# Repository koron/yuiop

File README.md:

# YUIOP Keyboard series

YUIOP keyboards are experimental original keyboards designed by KoRoN.

## Sub Projects

Keyboards in this project are:

*   yuiop27/ - separate keyboard prototype.

    27 keys for one hand. single left hand.

*   yuiop54/main - signle board keyboard prototype.

    combined right and left-hand boards of yuiop27.
    PCB dimension is 285.00mm x 94.60mm (GH60 compatible form factor without
    screw holes).

*   yuiop54/main2 - researching version of yuiop54.

    multi-sheets schematic.
    fix layout for auto routing.
    introduce GND cupper fill.
    *   rev.B - trial to make compatible with GH60 (include screw holes).

        use popular keycaps size.
        tring 128x64 dots OLED.
    *   rev.C - key sizes revised version.

        consider just layout.
        use 1u footprint for keys of little fingers. 
        compact form factor size, 267.00mm x 95.00mm (drop compatibility with
        GH60).
        change the origin to center of PCB.
        use 2u for R5 center key.
        use Edge.Cuts to represents screw holes.
        OLED is 128x32 dots.
    *   rev.D - narrowwer version of rev.C

        consider just layout.
        the dimension is 262.0mm x 95.00mm
        reduce margins between `F` and `G` keys, and `H` and `J` keys.
    *   rev.E - a variation of rev.C

        the dimension is 267.00mm x 95.00mm (same with rev.C, not rev.D)
        make keys on `F`'s row be able to use 1.25u keycap.

*   yuiop47/ - Single board keyborard with 47 keys.

    Shrink from yuiop54.
    PCB dimension is 214.00mm x 94.00mm

*   yuiop60hh/main - HHKB clone trial

    * main2 - HHKB clone trial #2
    * main3
    * main4
    * main5 - Practicing version
    * main5b - USB Type-C receptacle version of main5

*   yuiop50d/ - Small footprint, dense 50 keys keyboard.

    1u is 16mm, using small keycaps.
    Standard row staggered layout.
    Support Pro Micro and RapsberryPi Pico as MCU.
    PCB dimension is 182.00mm x 103.50mm

*   yuiop63hhs/ - Split HHKB layout minimal keyboard.

    No LED nor OLED, Just 63 (29+34) keys.
    PCB dimension 319.00mm x 95.00mm
    *   Left 152.50mm x 95.00mm
    *   Right 162.00mm x 95.00mm

*   yuiop22rs/ - 22 keys + rotary switch macropad.

    With OLED, without LED.
    PCB dimension 95.25mm x 95.25mm

*   contorller/ - Keyboard controler using ATmega32U4 which replacing Pro
    Micro.

*   yuiopPM/ - Pro Micro compatible but minimal for only keyboard, PCB

*   yuiopPM2/ - Revised version of yuiopPM. It was shelved unfinished.

*   yuiop60hh/main3 - HHKB layout, compatible with popular 60% cases.

    Problems on positions of screw hole or so. Not built.

*   yuiop60hh/main4 - HHKB layout, compatible with popular 60% cases.

    YUIOP60HH series revision 4.
    Implemented with MPU ATmega32U4 (not Pro Micro)

*   yuiop31rs/ - 31 keys + rotary switch macropad.

    With 31 LEDs (WB2812C-2020). Its hole is too small to be chaged extra on
    production.

*   yuiop60s/ - split keyboard prototype

*   yuiop60pi/ - PGA2040 (RP2040) base HHKB layout semi-compatible keyboard.

*   yuiop2040/ - Original RP2040 control board.

*   yuiop2040C/ "Compact" model of yuiop2040. Abandoned.

*   yuiop32dm/ - Experimental keyboard for Duplic Matrix

*   yuiopPD/ - Pointing device using the trackball module of Keyball series.

*   rp2040-controller/ - Reusable circuit diagram for controller using RP2040

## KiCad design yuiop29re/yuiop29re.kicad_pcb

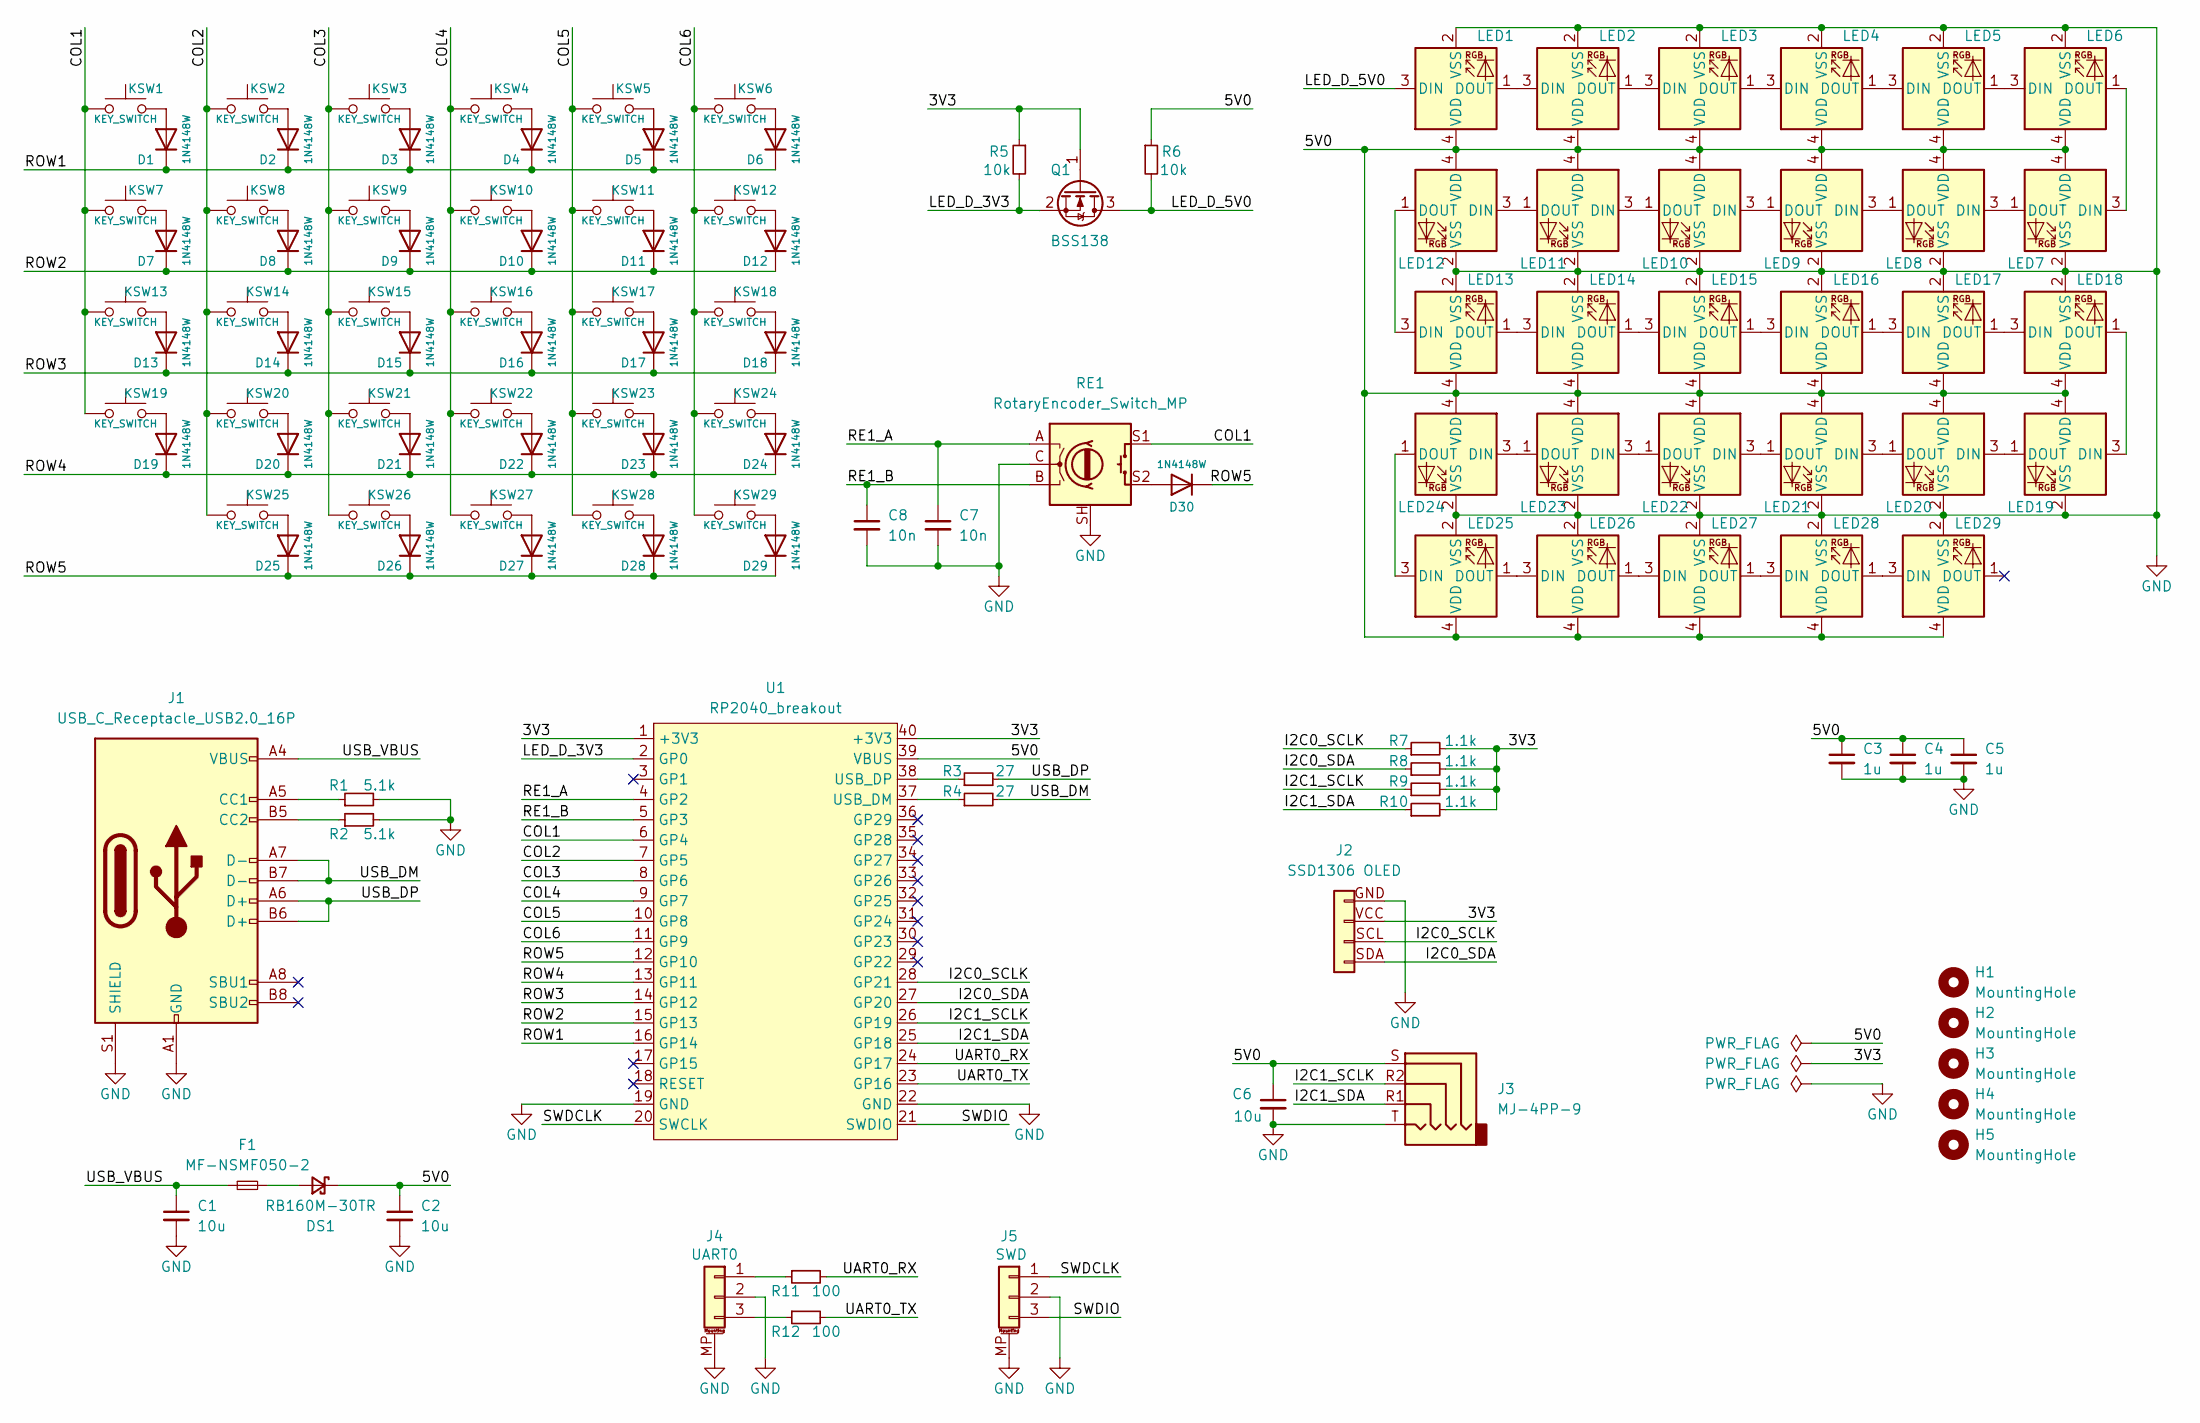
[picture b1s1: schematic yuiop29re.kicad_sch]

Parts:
C1, C2, C6: 10u; C_0603_1608Metric
C3, C4, C5: 1u; C_0603_1608Metric
C7, C8: 10n; C_0603_1608Metric
D1, D2, D3, D4, D5, D6, D7, D8, D9, D10, D11, D12, D13, D14, D15, D16, D17, D18, D19, D20, D21, D22, D23, D24, D25, D26, D27, D28, D29, D30: 1N4148W; D_SOD-123_v2
DS1: RB160M-30TR; D_SOD-123
F1: MF-NSMF050-2; Fuse_1206_3216Metric
H1, H2, H3, H4, H5: MountingHole; MountingHole_2.2mm_M2
J1: USB_C_Receptacle_USB2.0_16P; USB_C_Receptacle_XKB_U262-16XN-4BVC11
J2: SSD1306 OLED; OLED_128x32
J3: MJ-4PP-9; MJ-4PP-9_2021
J4: UART0; JST_SH_SM03B-SRSS-TB_1x03-1MP_P1.00mm_Horizontal
J5: SWD; JST_SH_SM03B-SRSS-TB_1x03-1MP_P1.00mm_Horizontal
KSW1, KSW2, KSW3, KSW4, KSW5, KSW6, KSW7, KSW8, KSW9, KSW10, KSW11, KSW12, KSW13, KSW14, KSW15, KSW16, KSW17, KSW18, KSW19, KSW20, KSW21, KSW22, KSW23, KSW24, KSW25, KSW26, KSW27, KSW28, KSW29: KEY_SWITCH; Cherry_MX_Hotswap_1.0u_v4
LED1, LED2, LED3, LED4, LED5, LED6, LED7, LED8, LED9, LED10, LED11, LED12, LED13, LED14, LED15, LED16, LED17, LED18, LED19, LED20, LED21, LED22, LED23, LED24, LED25, LED26, LED27, LED28, LED29: WS2812C-2020; LED_WS2812C-2020_BackMount_v2
Q1: BSS138; SOT-23
R1, R2: 5.1k; R_0603_1608Metric
R3, R4: 27; R_0603_1608Metric
R5, R6: 10k; R_0603_1608Metric
R7, R8, R9, R10: 1.1k; R_0603_1608Metric
R11, R12: 100; R_0603_1608Metric
RE1: RotaryEncoder_Switch_MP; RotaryEncoder_Bourns_Vertical_PEC12R-3x17F-Sxxxx
U1: RP2040_breakout; RP2040_Breakout-PTH

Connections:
/3V3: J2.VCC (Pin_2), Q1.1 (G), R5.1, R7.2, R8.2, R9.2, R10.2, U1.1 (+3V3), U1.40 (+3V3)
/5V0: C2.1, C3.1, C4.1, C5.1, C6.1, DS1.1 (K), J3.S, LED1.4 (VDD), LED2.4 (VDD), LED3.4 (VDD), LED4.4 (VDD), LED5.4 (VDD), LED6.4 (VDD), LED7.4 (VDD), LED8.4 (VDD), LED9.4 (VDD), LED10.4 (VDD), LED11.4 (VDD), LED12.4 (VDD), LED13.4 (VDD), LED14.4 (VDD), LED15.4 (VDD), LED16.4 (VDD), LED17.4 (VDD), LED18.4 (VDD), LED19.4 (VDD), LED20.4 (VDD), LED21.4 (VDD), LED22.4 (VDD), LED23.4 (VDD), LED24.4 (VDD), LED25.4 (VDD), LED26.4 (VDD), LED27.4 (VDD), LED28.4 (VDD), LED29.4 (VDD), R6.1, U1.39 (VBUS)
/COL1: KSW1.1, KSW7.1, KSW13.1, KSW19.1, RE1.S1, U1.6 (GP4)
/COL2: KSW2.1, KSW8.1, KSW14.1, KSW20.1, KSW25.1, U1.7 (GP5)
/COL3: KSW3.1, KSW9.1, KSW15.1, KSW21.1, KSW26.1, U1.8 (GP6)
/COL4: KSW4.1, KSW10.1, KSW16.1, KSW22.1, KSW27.1, U1.9 (GP7)
/COL5: KSW5.1, KSW11.1, KSW17.1, KSW23.1, KSW28.1, U1.10 (GP8)
/COL6: KSW6.1, KSW12.1, KSW18.1, KSW24.1, KSW29.1, U1.11 (GP9)
/I2C0_SCLK: J2.SCL (Pin_3), R7.1, U1.28 (GP21)
/I2C0_SDA: J2.SDA (Pin_4), R8.1, U1.27 (GP20)
/I2C1_SCLK: J3.R2, R9.1, U1.26 (GP19)
/I2C1_SDA: J3.R1, R10.1, U1.25 (GP18)
/LED_D_3V3: Q1.2 (S), R5.2, U1.2 (GP0)
/LED_D_5V0: LED1.3 (DIN), Q1.3 (D), R6.2
/RE1_A: C7.1, RE1.A, U1.4 (GP2)
/RE1_B: C8.1, RE1.B, U1.5 (GP3)
/ROW1: D1.1 (K), D2.1 (K), D3.1 (K), D4.1 (K), D5.1 (K), D6.1 (K), U1.16 (GP14)
/ROW2: D7.1 (K), D8.1 (K), D9.1 (K), D10.1 (K), D11.1 (K), D12.1 (K), U1.15 (GP13)
/ROW3: D13.1 (K), D14.1 (K), D15.1 (K), D16.1 (K), D17.1 (K), D18.1 (K), U1.14 (GP12)
/ROW4: D19.1 (K), D20.1 (K), D21.1 (K), D22.1 (K), D23.1 (K), D24.1 (K), U1.13 (GP11)
/ROW5: D25.1 (K), D26.1 (K), D27.1 (K), D28.1 (K), D29.1 (K), D30.1 (K), U1.12 (GP10)
/SWDCLK: J5.1, U1.20 (SWCLK)
/SWDIO: J5.3, U1.21 (SWDIO)
/UART0_RX: R11.2, U1.24 (GP17)
/UART0_TX: R12.2, U1.23 (GP16)
/USB_DM: J1.A7 (D-), J1.B7 (D-), R4.2
/USB_DP: J1.A6 (D+), J1.B6 (D+), R3.2
/USB_VBUS: C1.1, F1.1, J1.A4 (VBUS), J1.A9 (VBUS), J1.B4 (VBUS), J1.B9 (VBUS)
GND: C1.2, C2.2, C3.2, C4.2, C5.2, C6.2, C7.2, C8.2, J1.A1 (GND), J1.A12 (GND), J1.B1 (GND), J1.B12 (GND), J1.S1 (SHIELD), J2.GND (Pin_1), J3.T, J4.2, J4.MP (MountPin), J5.2, J5.MP (MountPin), LED1.2 (VSS), LED2.2 (VSS), LED3.2 (VSS), LED4.2 (VSS), LED5.2 (VSS), LED6.2 (VSS), LED7.2 (VSS), LED8.2 (VSS), LED9.2 (VSS), LED10.2 (VSS), LED11.2 (VSS), LED12.2 (VSS), LED13.2 (VSS), LED14.2 (VSS), LED15.2 (VSS), LED16.2 (VSS), LED17.2 (VSS), LED18.2 (VSS), LED19.2 (VSS), LED20.2 (VSS), LED21.2 (VSS), LED22.2 (VSS), LED23.2 (VSS), LED24.2 (VSS), LED25.2 (VSS), LED26.2 (VSS), LED27.2 (VSS), LED28.2 (VSS), LED29.2 (VSS), R1.2, R2.2, RE1.C, RE1.SH, U1.19 (GND), U1.22 (GND)
unnamed: D1.2 (A), KSW1.2
unnamed: D2.2 (A), KSW2.2
unnamed: D3.2 (A), KSW3.2
unnamed: D4.2 (A), KSW4.2
unnamed: D5.2 (A), KSW5.2
unnamed: D6.2 (A), KSW6.2
unnamed: D7.2 (A), KSW7.2
unnamed: D8.2 (A), KSW8.2
unnamed: D9.2 (A), KSW9.2
unnamed: D10.2 (A), KSW10.2
unnamed: D11.2 (A), KSW11.2
unnamed: D12.2 (A), KSW12.2
unnamed: D13.2 (A), KSW13.2
unnamed: D14.2 (A), KSW14.2
unnamed: D15.2 (A), KSW15.2
unnamed: D16.2 (A), KSW16.2
unnamed: D17.2 (A), KSW17.2
unnamed: D18.2 (A), KSW18.2
unnamed: D19.2 (A), KSW19.2
unnamed: D20.2 (A), KSW20.2
unnamed: D21.2 (A), KSW21.2
unnamed: D22.2 (A), KSW22.2
unnamed: D23.2 (A), KSW23.2
unnamed: D24.2 (A), KSW24.2
unnamed: D25.2 (A), KSW25.2
unnamed: D26.2 (A), KSW26.2
unnamed: D27.2 (A), KSW27.2
unnamed: D28.2 (A), KSW28.2
unnamed: D29.2 (A), KSW29.2
unnamed: D30.2 (A), RE1.S2
unnamed: DS1.2 (A), F1.2
unnamed: J1.A5 (CC1), R1.1
unnamed: J1.B5 (CC2), R2.1
unnamed: J4.1, R11.1
unnamed: J4.3, R12.1
unnamed: LED1.1 (DOUT), LED2.3 (DIN)
unnamed: LED2.1 (DOUT), LED3.3 (DIN)
unnamed: LED3.1 (DOUT), LED4.3 (DIN)
unnamed: LED4.1 (DOUT), LED5.3 (DIN)
unnamed: LED5.1 (DOUT), LED6.3 (DIN)
unnamed: LED6.1 (DOUT), LED7.3 (DIN)
unnamed: LED7.1 (DOUT), LED8.3 (DIN)
unnamed: LED8.1 (DOUT), LED9.3 (DIN)
unnamed: LED9.1 (DOUT), LED10.3 (DIN)
unnamed: LED10.1 (DOUT), LED11.3 (DIN)
unnamed: LED11.1 (DOUT), LED12.3 (DIN)
unnamed: LED12.1 (DOUT), LED13.3 (DIN)
unnamed: LED13.1 (DOUT), LED14.3 (DIN)
unnamed: LED14.1 (DOUT), LED15.3 (DIN)
unnamed: LED15.1 (DOUT), LED16.3 (DIN)
unnamed: LED16.1 (DOUT), LED17.3 (DIN)
unnamed: LED17.1 (DOUT), LED18.3 (DIN)
unnamed: LED18.1 (DOUT), LED19.3 (DIN)
unnamed: LED19.1 (DOUT), LED20.3 (DIN)
unnamed: LED20.1 (DOUT), LED21.3 (DIN)
unnamed: LED21.1 (DOUT), LED22.3 (DIN)
unnamed: LED22.1 (DOUT), LED23.3 (DIN)
unnamed: LED23.1 (DOUT), LED24.3 (DIN)
unnamed: LED24.1 (DOUT), LED25.3 (DIN)
unnamed: LED25.1 (DOUT), LED26.3 (DIN)
unnamed: LED26.1 (DOUT), LED27.3 (DIN)
unnamed: LED27.1 (DOUT), LED28.3 (DIN)
unnamed: LED28.1 (DOUT), LED29.3 (DIN)
unnamed: R4.1, U1.37 (USB_DM)
unnamed: R3.1, U1.38 (USB_DP)

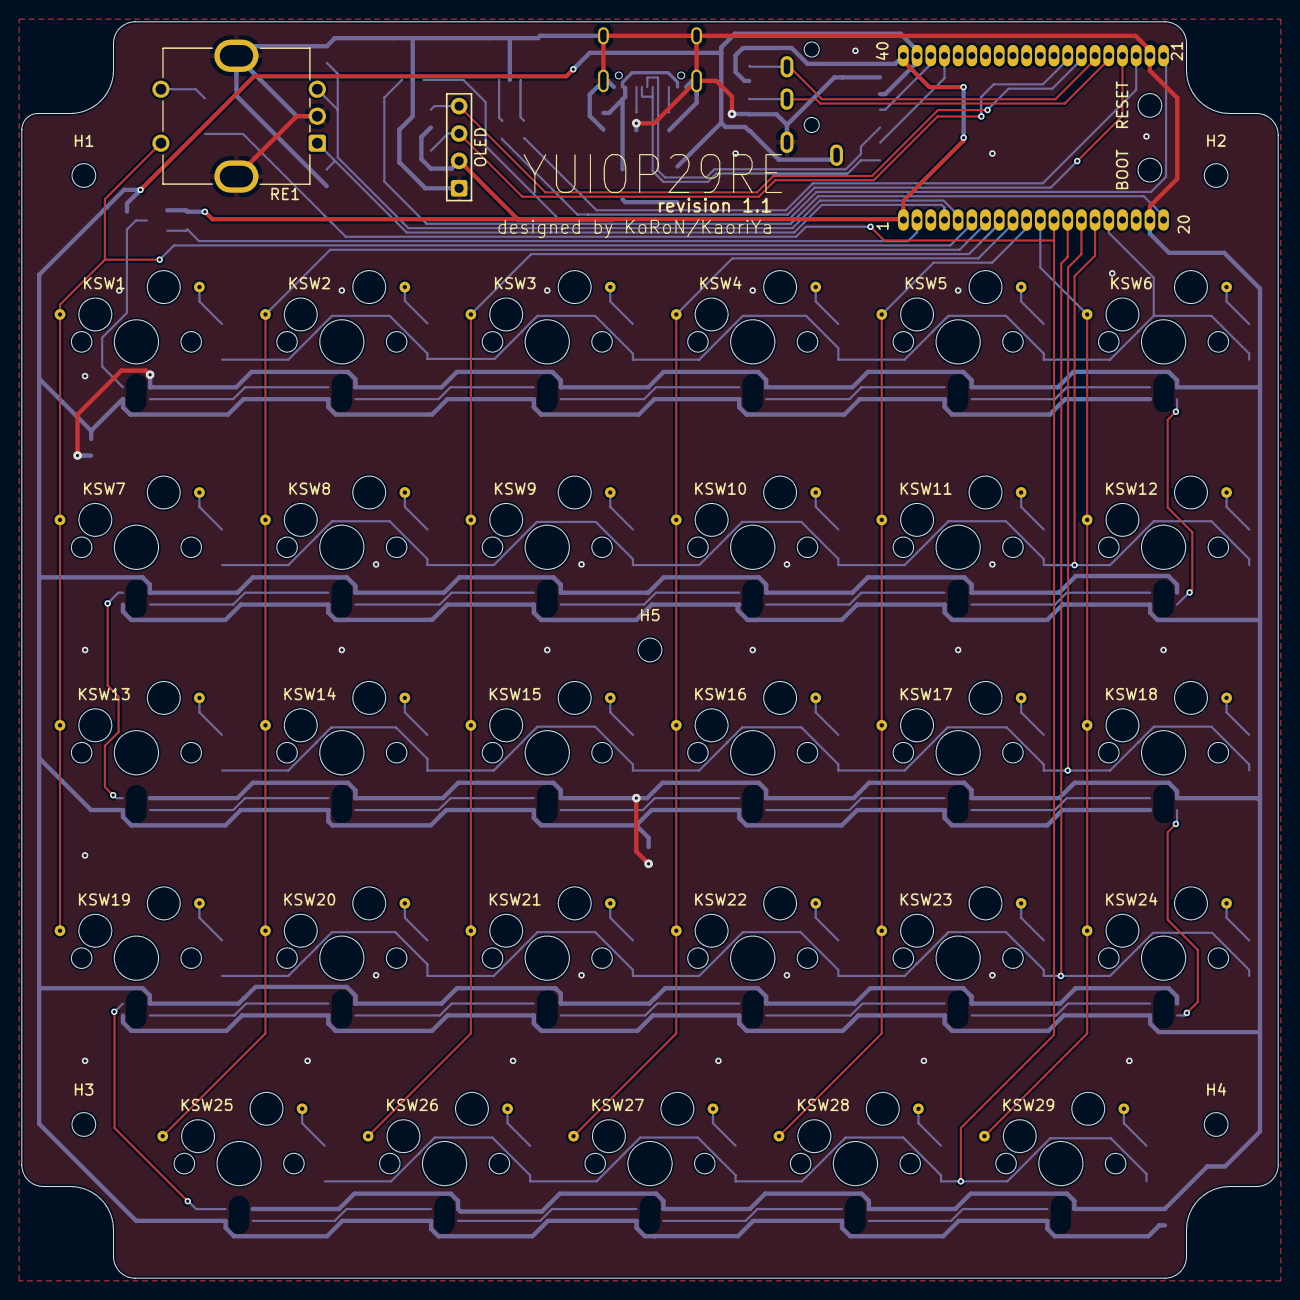
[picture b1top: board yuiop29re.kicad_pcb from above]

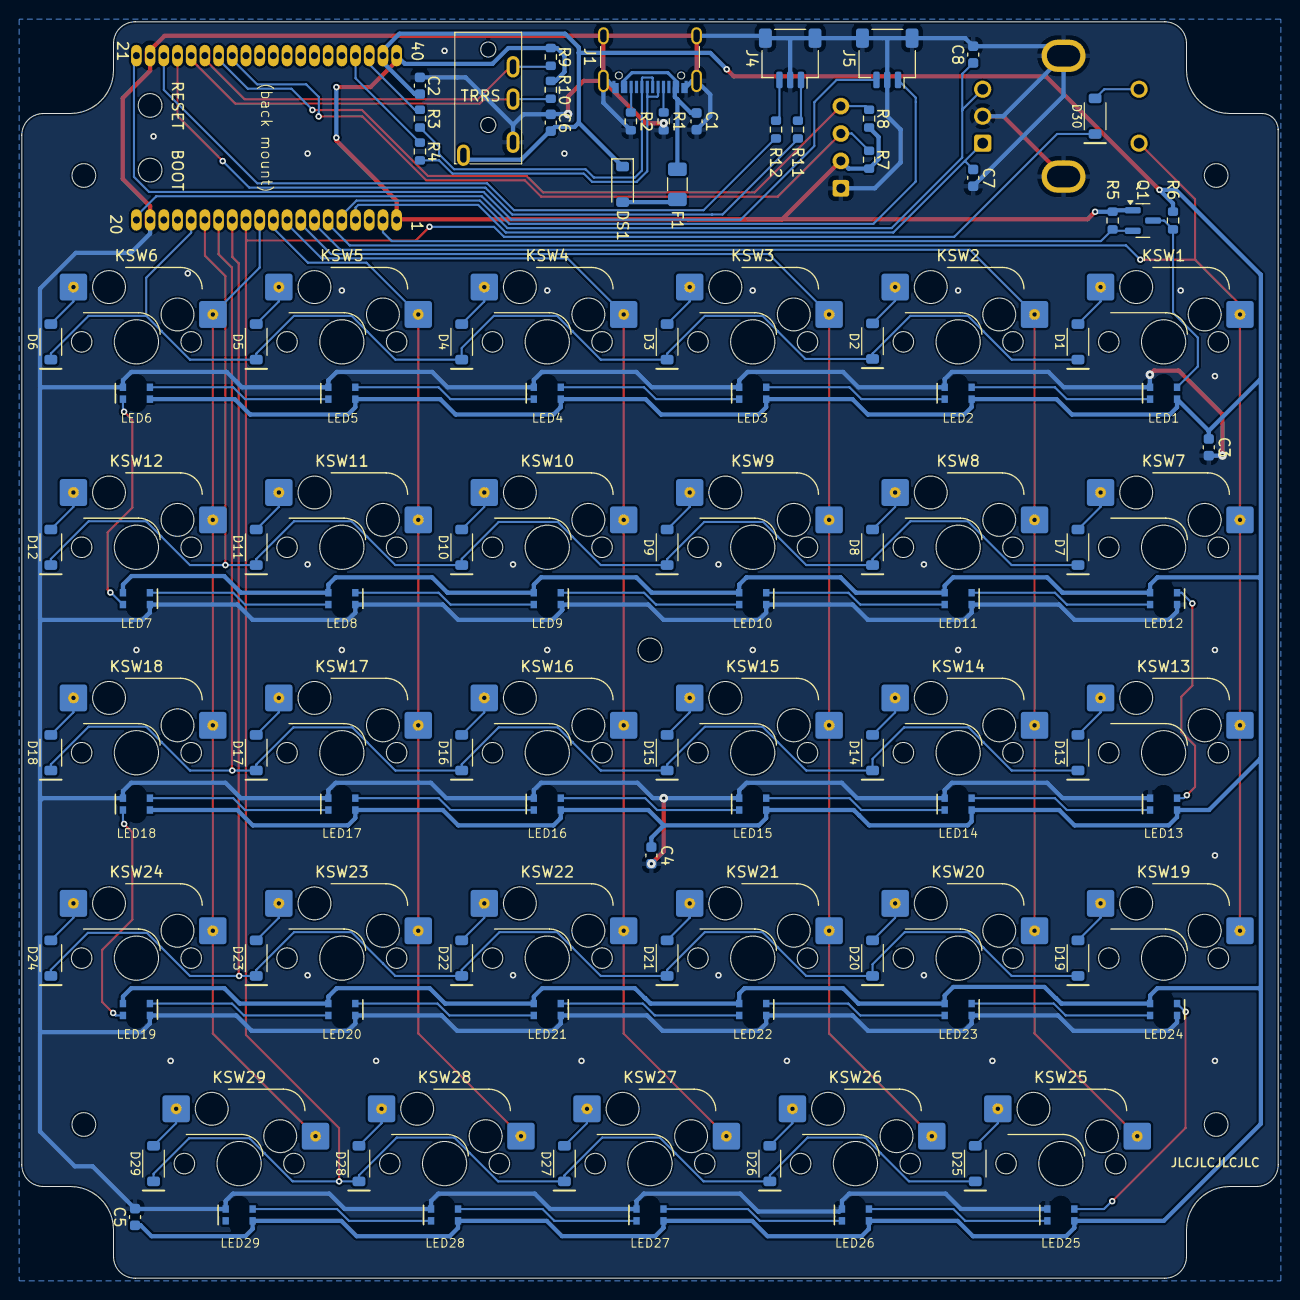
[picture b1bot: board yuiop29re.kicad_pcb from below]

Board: 2 copper layers, 116.5 x 116.5 mm, 123 parts (27 on the bottom side), 94 nets.

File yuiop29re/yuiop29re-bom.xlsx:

Reference | Value | Qty | C/Qty | R/Qty | Shop URL | Lot | Price | Purpose | Full price | Mid price | Low price
C1,C2,C6 | 10uF | 3 | 3 | 3 | https://akizukidenshi.com/catalog/g/g113161/ | 10 | 150 | 5.0V電源周りの安定化デンゲンマワアンテイカ | 45 | 45 | 45
C3,C4,C5 | 1uF | 3 | 3 | 0 | https://akizukidenshi.com/catalog/g/g114526/ https://akizukidenshi.com/catalog/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 | 20 | 200 | LEDの安定化アンテイカ | 30 | 30 | 0
C7,C8 | 10nF (0.01uF) | 2 | 0 | 0 | https://akizukidenshi.com/catalog/g/g113387/ | 50 | 100 | ロータリーエンコーダーのノイズフィルタ | 4 | 0 | 0
D1~30 | 1N4148W | 30 | 30 | 30 | https://akizukidenshi.com/catalog/g/g107084/ | 40 | 150 | キーマトリックス | 112.5 | 112.5 | 112.5
DS1 | RB160M-30TR | 1 | 1 | 1 | https://akizukidenshi.com/catalog/g/g101398/ | 10 | 150 | 電源デンゲン | 15 | 15 | 15
F1 | MF-NSMF050-2 | 1 | 1 | 1 | https://akizukidenshi.com/catalog/g/g115300/ | 4 | 100 | 電源デンゲン | 25 | 25 | 25
J1 | 5077CR-16-SMC2-BK-TR | 1 | 1 | 1 | https://akizukidenshi.com/catalog/g/g114356/ | 1 | 110 | USB Type-C レセプタクル | 110 | 110 | 110
J2 | SSD1306 OLED | 1 | 1 | 1 | https://www.amazon.co.jp/gp/product/B085C67PF1/ | 3 | 1450 | OLED表示ヒョウジ | 483.33333333333331 | 483.33333333333331 | 483.33333333333331
J3 | MJ-4PP-9 | 1 | 1 | 0 | https://akizukidenshi.com/catalog/g/g106070/ | 1 | 50 | TRRS | 50 | 50 | 0
J4 | UART0 | 1 | 0 | 0 | https://jp.rs-online.com/web/p/pcb-headers/5151507 | 10 | 946 | デバッグ用ヨウ | 94.6 | 0 | 0
J5 | SWD | 1 | 0 | 0 | https://jp.rs-online.com/web/p/pcb-headers/5151507 | 10 | 946 | デバッグ用ヨウ | 94.6 | 0 | 0
KSW1~29 | KEY_SWITCH | 29 | 29 | 29 | https://talpkeyboard.net/items/5e02c5405b120c792616bcf9 | 10 | 180 | キーマトリックス | 522 | 522 | 522
LED1~29 | WS2812C-2020 | 29 | 29 | 0 | https://akizukidenshi.com/catalog/g/g115068/ | 10 | 200 | LED | 580 | 580 | 0
Q1 | BSS138 | 1 | 1 | 0 | https://akizukidenshi.com/catalog/g/g104232/ | 25 | 100 | LED | 4 | 4 | 0
R1,R2 | 5.1kΩ | 2 | 2 | 2 | https://www.sengoku.co.jp/mod/sgk_cart/detail.php?code=EEHD-57GS | 50 | 210 | USB CC | 8.4 | 8.4 | 8.4
R3,R4 | 27Ω | 2 | 2 | 2 | https://www.sengoku.co.jp/mod/sgk_cart/detail.php?code=EEHD-57FF | 50 | 210 | USB D+/- | 8.4 | 8.4 | 8.4
R5,R6 | 10kΩ | 2 | 2 | 0 | https://www.sengoku.co.jp/mod/sgk_cart/detail.php?code=EEHD-57GX | 50 | 210 | LED | 8.4 | 8.4 | 0
R7,R8,R9,R10 | 1.1kΩ(1.0kΩ) | 4 | 0 | 0 | https://www.sengoku.co.jp/mod/sgk_cart/detail.php?code=EEHD-57GK | 50 | 210 | I2C (OLED, TRRS) pull up | 16.8 | 0 | 0
R11,R12 | 100Ω | 2 | 0 | 0 | https://www.sengoku.co.jp/mod/sgk_cart/detail.php?code=EEHD-57FV | 50 | 210 | SWD | 8.4 | 0 | 0
RE1 | PEC12R-4220F-S0024 | 1 | 1 | 1 | https://jp.rs-online.com/web/p/mechanical-rotary-encoders/7377773 | 1 | 275 | ロータリーエンコーダー | 275 | 275 | 275
U1 | Picossci RP2040 | 1 | 1 | 1 | https://www.switch-science.com/products/8440 | 1 | 1760 | MCU | 1760 | 1760 | 1760
 | FSS-71034-20 | 2 | 2 | 2 | https://www.hirosugi-net.co.jp/shop/g/g18851/ | 10 | 638 | 1.27mm ソケット 20ピン (H3.5mm) | 127.6 | 127.6 | 127.6
 | PSS-710103-20 | 2 | 2 | 2 | https://www.hirosugi-net.co.jp/shop/g/g18575/ | 50 | 2090 | 1.27mm ピンヘッダー 20ピン (H1.0mm) | 83.6 | 83.6 | 83.6
ケース | TW13-3-13 | 1 | 1 | 1 | https://www.sengoku.co.jp/mod/sgk_cart/detail.php?code=EEHD-0JXH | 1 | 420 | 要加工ヨウカコウ | 420 | 420 | 420
 | ASB-2003.5E | 5 | 4 | 0 | https://www.hirosugi-net.co.jp/shop/g/g58/ | 50 | 1300 | スペーサー M2 3.5 | 130 | 104 | 0
 | FX-0230EB | 10 | 8 | 0 | https://www.amazon.co.jp/gp/product/B00MIA9V00 | 180 | 990 | 低頭精密小ねじ M2x3 黒テイトウセイミツコクロ | 55 | 44 | 0
 | 10179185 | 4 | 4 | 4 | https://www.amazon.co.jp/dp/B01MZXDBAY | 12 | 191 | 超低頭タッピングねじ M3x12チョウテイトウ | 63.666666666666664 | 63.666666666666664 | 63.666666666666664
基板キバン |  | 1 | 1 | 1 |  | 5 | 6000 | JLCPCB | 1200 | 1200 | 1200
Total |  |  |  |  |  |  |  |  | 6335.300000000002 | 6079.9000000000015 | 5259.5
x1.3 |  |  |  |  |  |  |  |  | 8235.8900000000031 | 7903.8700000000017 | 6837.35
x2.0 |  |  |  |  |  |  |  |  | 12670.600000000004 | 12159.800000000003 | 10519

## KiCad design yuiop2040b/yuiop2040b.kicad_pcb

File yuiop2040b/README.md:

# YUIOP2040b

回路図中の各コンポーネントをページに分割することで
再利用しやすくすることを目的とした版。

## Parts List

Ref	|Value
--------|--------------
C1-C3   | 10μF
C4,C5   | 10pF or 15 pF
C6,C7   | 1μF
C8-C17  | 100nF (0.1μF)
R1,R2   | 27Ω
R3,R5,R6| 1kΩ
R4      | 10kΩ
R31,R32 | 5.1kΩ
U1      | MIC5219-3.3YM5
U2      | RP2040
U3      | W25Q16JVSS
Y1      | FA238V 12.000000MHz 10.0 +50.0-50.0
J1      | USB micro B
J2      | USB C Receptacle USB 2.0
DS1     | RB160M-30TR
F1      | MF-NSMF050-2

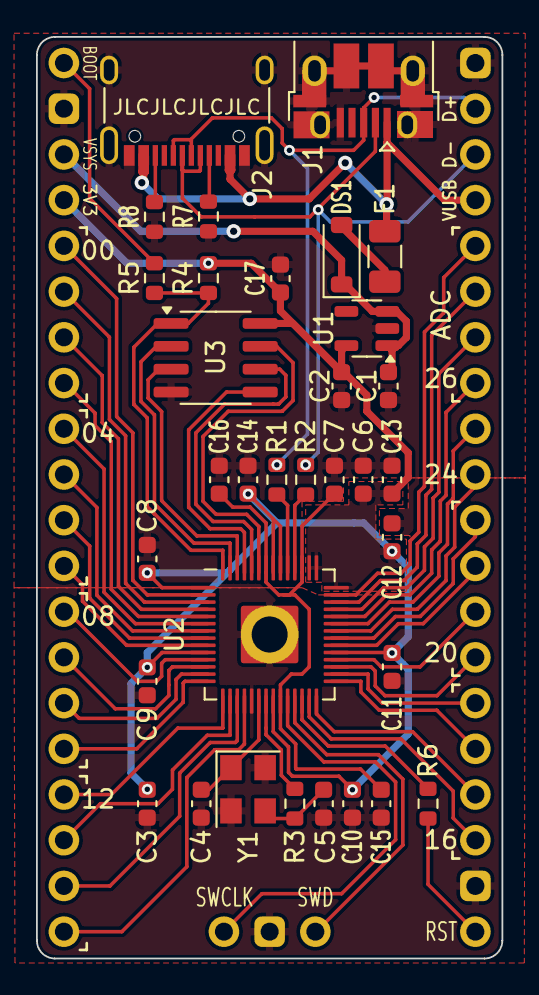
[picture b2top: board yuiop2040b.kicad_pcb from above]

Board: 2 copper layers, 25.9 x 51.2 mm, 36 parts (0 on the bottom side), 56 nets.

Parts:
C1, C2, C3: 10u; C_0603_1608Metric
C4, C5: 10p; C_0603_1608Metric
C6, C7: 1u; C_0603_1608Metric
C8, C9, C10, C11, C12, C13, C14, C15, C16, C17: 100n; C_0603_1608Metric
DS1: RB160M-30TR; D_SOD-123
F1: MF-NSMF050-2; Fuse_1206_3216Metric
J1: USB_B_Micro; USB_Micro-B_Amphenol_10103594-0001LF_Horizontal
J2: USB_C_Receptacle_USB2.0; USB_C_Receptacle_XKB_U262-16XN-4BVC11
J3, J4: Conn_01x20; PinHeader_1x20_P2.54mm_Vertical
J5: Conn_01x03; PinHeader_1x03_P2.54mm_Vertical
R1, R2: 27; R_0603_1608Metric
R3, R5, R6: 1k; R_0603_1608Metric
R4: 10k; R_0603_1608Metric
R7, R8: 5.1k; R_0603_1608Metric
U1: MIC5219-3.3YM5; SOT-23-5
U2: RP2040; RP2040-QFN-56-r2
U3: W25Q16JVSS; SOIC-8_3.9x4.9mm_P1.27mm
Y1: FA238V 12.000000MHz 10.0 +50.0-50.0; Crystal_SMD_SeikoEpson_FA238V-4Pin_3.2x2.5mm

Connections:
+1V1: C7.1, C15.1, C16.1, U2.23 (DVDD), U2.45 (VREG_VOUT), U2.50 (DVDD)
+3V3: C2.1, C3.1, C6.1, C8.1, C9.1, C10.1, C11.1, C12.1, C13.1, C14.1, C17.1, J3.4, R4.2, U1.5 (OUT), U2.1 (IOVDD), U2.10 (IOVDD), U2.22 (IOVDD), U2.33 (IOVDD), U2.42 (IOVDD), U2.43 (ADC_AVDD), U2.44 (VREG_IN), U2.48 (USB_VDD), U2.49 (IOVDD), U3.8 (VCC)
/BOOTSEL: J3.1, R5.1
/GPIO0: J3.5, U2.2 (GPIO0)
/GPIO1: J3.6, U2.3 (GPIO1)
/GPIO2: J3.7, U2.4 (GPIO2)
/GPIO3: J3.8, U2.5 (GPIO3)
/GPIO4: J3.9, U2.6 (GPIO4)
/GPIO5: J3.10, U2.7 (GPIO5)
/GPIO6: J3.11, U2.8 (GPIO6)
/GPIO7: J3.12, U2.9 (GPIO7)
/GPIO8: J3.13, U2.11 (GPIO8)
/GPIO9: J3.14, U2.12 (GPIO9)
/GPIO10: J3.15, U2.13 (GPIO10)
/GPIO11: J3.16, U2.14 (GPIO11)
/GPIO12: J3.17, U2.15 (GPIO12)
/GPIO13: J3.18, U2.16 (GPIO13)
/GPIO14: J3.19, U2.17 (GPIO14)
/GPIO15: J3.20, U2.18 (GPIO15)
/GPIO16: J4.3, U2.27 (GPIO16)
/GPIO17: J4.4, U2.28 (GPIO17)
/GPIO18: J4.5, U2.29 (GPIO18)
/GPIO19: J4.6, U2.30 (GPIO19)
/GPIO20: J4.7, U2.31 (GPIO20)
/GPIO21: J4.8, U2.32 (GPIO21)
/GPIO22: J4.9, U2.34 (GPIO22)
/GPIO23: J4.10, U2.35 (GPIO23)
/GPIO24: J4.11, U2.36 (GPIO24)
/GPIO25: J4.12, U2.37 (GPIO25)
/GPIO26_ADC0: J4.13, U2.38 (GPIO26_ADC0)
/GPIO27_ADC1: J4.14, U2.39 (GPIO27_ADC1)
/GPIO28_ADC2: J4.15, U2.40 (GPIO28_ADC2)
/GPIO29_ADC3: J4.16, U2.41 (GPIO29_ADC3)
/QSPI_SCLK: U2.52 (QSPI_SCLK), U3.6 (CLK)
/QSPI_SD0: U2.53 (QSPI_SD0), U3.5 (DI(IO0))
/QSPI_SD1: U2.55 (QSPI_SD1), U3.2 (DO(IO1))
/QSPI_SD2: U2.54 (QSPI_SD2), U3.3 (IO2)
/QSPI_SD3: U2.51 (QSPI_SD3), U3.7 (IO3)
/QSPI_SS: R4.1, R5.2, U2.56 (QSPI_SS), U3.1 (~CS)
/RESET: J4.1, R6.1
/RUN: R6.2, U2.26 (RUN)
/SWCLK: J5.1, U2.24 (SWCLK)
/SWD: J5.3, U2.25 (SWD)
/USB_D+: J1.3 (D+), J2.A6 (D+), J2.B6 (D+), J4.19, R1.2
/USB_D-: J1.2 (D-), J2.A7 (D-), J2.B7 (D-), J4.18, R2.2
/USB_VBUS: F1.1, J1.1 (VBUS), J2.A4 (VBUS), J2.A9 (VBUS), J2.B4 (VBUS), J2.B9 (VBUS), J4.17
/VSYS: C1.1, DS1.1 (K), J3.3, U1.1 (IN), U1.3 (EN)
/XIN: C4.2, U2.20 (XIN), Y1.1
/XOUT: R3.2, U2.21 (XOUT)
GND: C1.2, C2.2, C3.2, C4.1, C5.1, C6.2, C7.2, C8.2, C9.2, C10.2, C11.2, C12.2, C13.2, C14.2, C15.2, C16.2, C17.2, J1.5 (GND), J1.6 (Shield), J2.A1 (GND), J2.A12 (GND), J2.B1 (GND), J2.B12 (GND), J2.S1 (SHIELD), J3.2, J4.2, J4.20, J5.2, R7.2, R8.2, U1.2 (GND), U2.19 (TESTEN), U2.57 (GND), U3.4 (GND), Y1.2, Y1.4
unnamed: C5.2, R3.1, Y1.3
unnamed: DS1.2 (A), F1.2
unnamed: J2.A5 (CC1), R7.1
unnamed: J2.B5 (CC2), R8.1
unnamed: R1.1, U2.47 (USB_DP)
unnamed: R2.1, U2.46 (USB_DM)

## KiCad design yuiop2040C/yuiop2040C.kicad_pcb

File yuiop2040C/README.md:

# YUIOP2040/C

"Compact" model of YUIOP2040.

* 16mm x 25.4mm ~ 35mm
    * 15.24mm =  600mil
    * 16.00mm =  630mil
    * 35.56mm = 1400mil
    * 25.4mm  = 1000mil
    * 30.48mm = 1200mil
    * 32.00mm = 1260mil

    16mm x 32mm, looks better.

* 1.25mm pitch pin header (20 x 2)
* Out All GPIO pins
* No USB receptacle (input by 4 pins)
* One side SMD

## Memo

* 1.25mm pitch pin header dimensions: 25.4mm x 2.1mm x 1.5mm

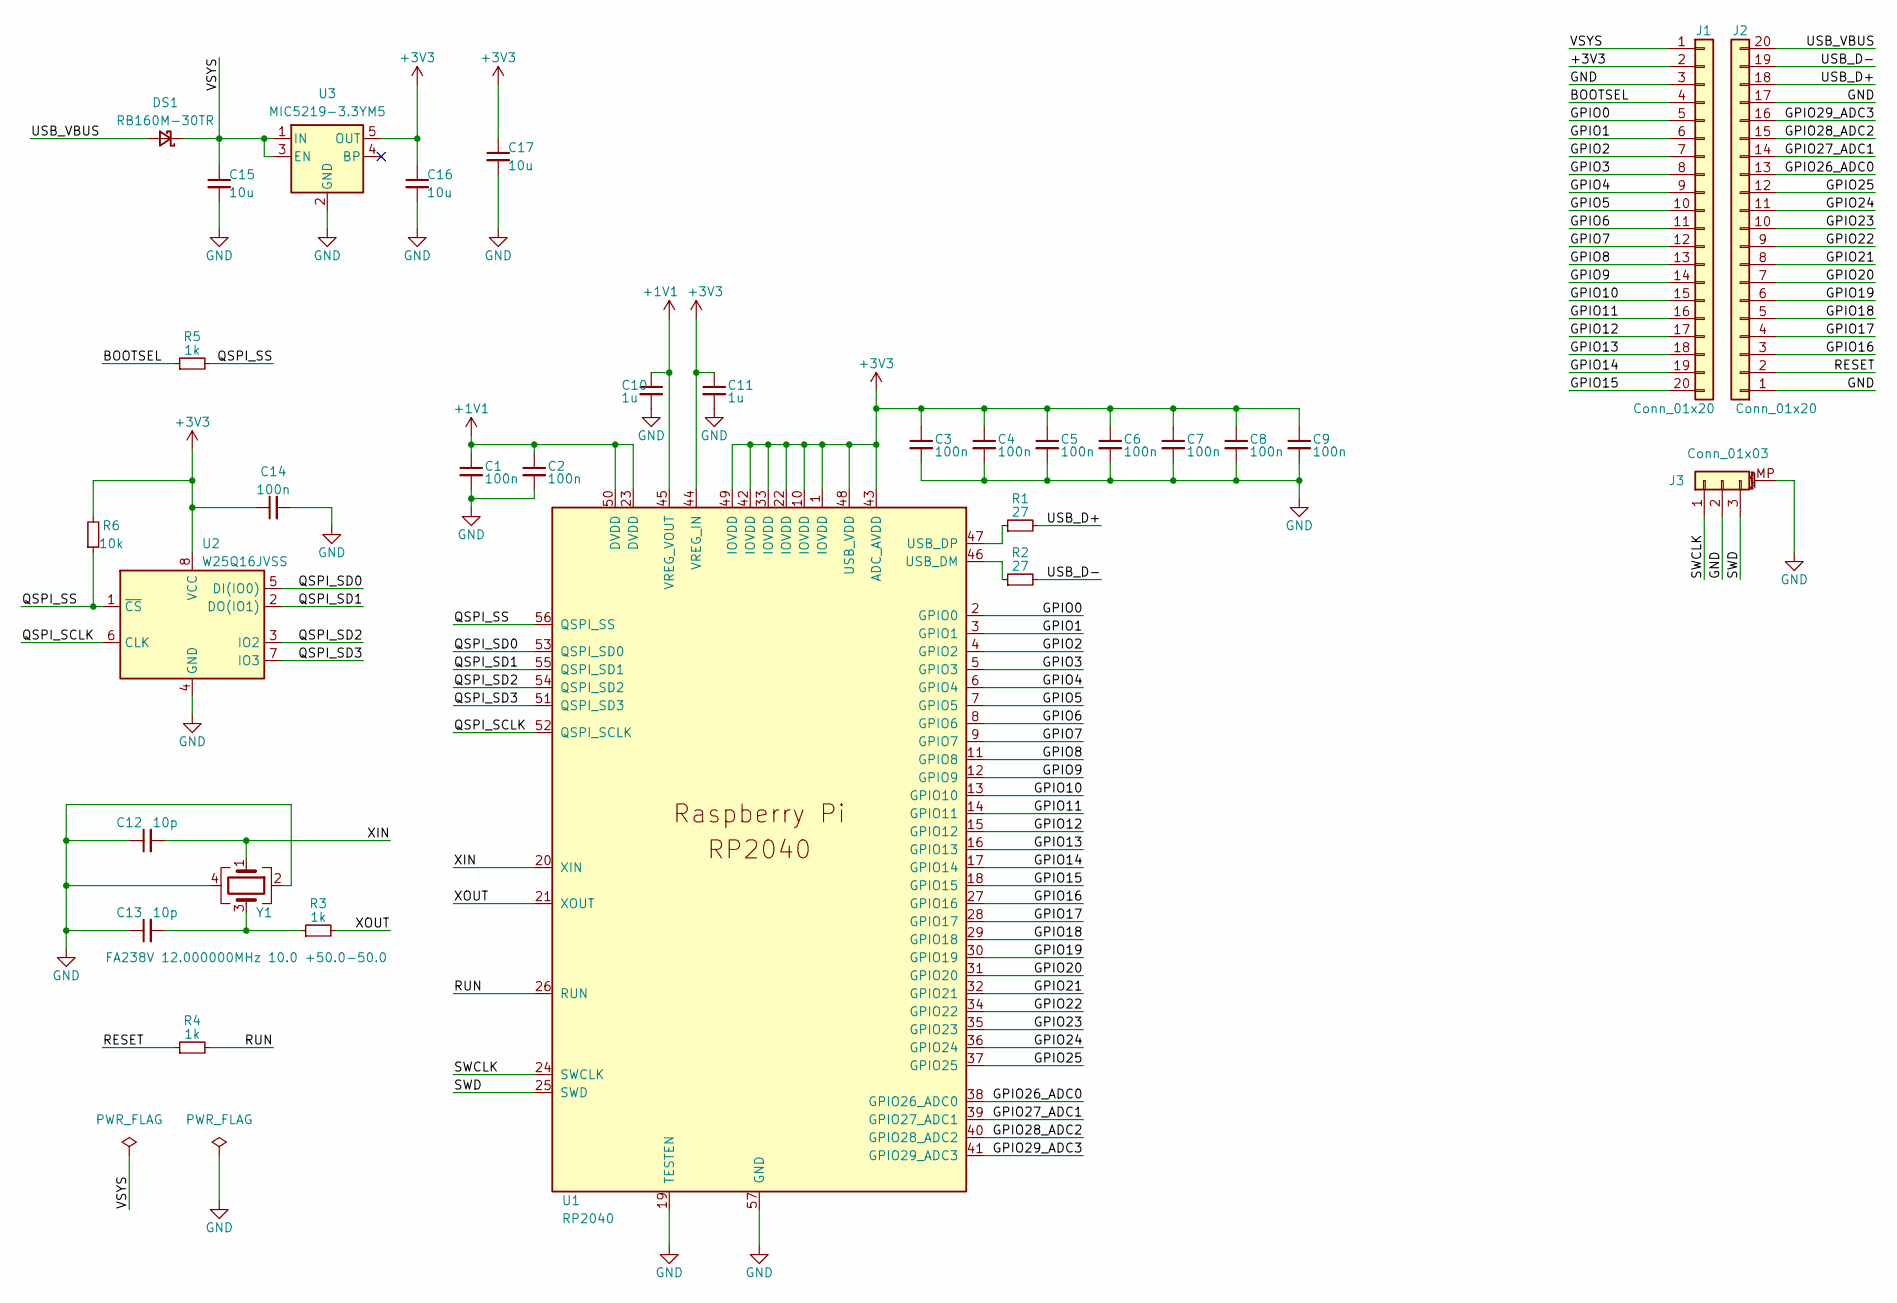
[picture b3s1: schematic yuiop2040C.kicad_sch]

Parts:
C1, C2, C3, C4, C5, C6, C7, C8, C9, C14: 100n; C_0402_1005Metric
C10, C11: 1u; C_0603_1608Metric
C12, C13: 10p; C_0402_1005Metric
C15, C16, C17: 10u; C_0603_1608Metric
DS1: RB160M-30TR; D_SOD-123
J1, J2: Conn_01x20; PinHeader_1x20_P1.27mm_Vertical
J3: Conn_01x03; JST_GH_SM03B-GHS-TB_1x03-1MP_P1.25mm_Horizontal
R1, R2: 27; R_0402_1005Metric
R3, R4, R5: 1k; R_0402_1005Metric
R6: 10k; R_0402_1005Metric
U1: RP2040; RP2040-QFN-56
U2: W25Q16JVSS; SOIC-8_3.9x4.9mm_P1.27mm
U3: MIC5219-3.3YM5; SOT-23-5
Y1: FA238V 12.000000MHz 10.0 +50.0-50.0; Crystal_SMD_SeikoEpson_FA238V-4Pin_3.2x2.5mm

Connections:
+1V1: C1.1, C2.1, C10.1, U1.23 (DVDD), U1.45 (VREG_VOUT), U1.50 (DVDD)
+3V3: C3.1, C4.1, C5.1, C6.1, C7.1, C8.1, C9.1, C11.1, C14.1, C16.1, C17.1, J1.2, R6.2, U1.1 (IOVDD), U1.10 (IOVDD), U1.22 (IOVDD), U1.33 (IOVDD), U1.42 (IOVDD), U1.43 (ADC_AVDD), U1.44 (VREG_IN), U1.48 (USB_VDD), U1.49 (IOVDD), U2.8 (VCC), U3.5 (OUT)
/BOOTSEL: J1.4, R5.1
/GPIO0: J1.5, U1.2 (GPIO0)
/GPIO1: J1.6, U1.3 (GPIO1)
/GPIO2: J1.7, U1.4 (GPIO2)
/GPIO3: J1.8, U1.5 (GPIO3)
/GPIO4: J1.9, U1.6 (GPIO4)
/GPIO5: J1.10, U1.7 (GPIO5)
/GPIO6: J1.11, U1.8 (GPIO6)
/GPIO7: J1.12, U1.9 (GPIO7)
/GPIO8: J1.13, U1.11 (GPIO8)
/GPIO9: J1.14, U1.12 (GPIO9)
/GPIO10: J1.15, U1.13 (GPIO10)
/GPIO11: J1.16, U1.14 (GPIO11)
/GPIO12: J1.17, U1.15 (GPIO12)
/GPIO13: J1.18, U1.16 (GPIO13)
/GPIO14: J1.19, U1.17 (GPIO14)
/GPIO15: J1.20, U1.18 (GPIO15)
/GPIO16: J2.3, U1.27 (GPIO16)
/GPIO17: J2.4, U1.28 (GPIO17)
/GPIO18: J2.5, U1.29 (GPIO18)
/GPIO19: J2.6, U1.30 (GPIO19)
/GPIO20: J2.7, U1.31 (GPIO20)
/GPIO21: J2.8, U1.32 (GPIO21)
/GPIO22: J2.9, U1.34 (GPIO22)
/GPIO23: J2.10, U1.35 (GPIO23)
/GPIO24: J2.11, U1.36 (GPIO24)
/GPIO25: J2.12, U1.37 (GPIO25)
/GPIO26_ADC0: J2.13, U1.38 (GPIO26_ADC0)
/GPIO27_ADC1: J2.14, U1.39 (GPIO27_ADC1)
/GPIO28_ADC2: J2.15, U1.40 (GPIO28_ADC2)
/GPIO29_ADC3: J2.16, U1.41 (GPIO29_ADC3)
/QSPI_SCLK: U1.52 (QSPI_SCLK), U2.6 (CLK)
/QSPI_SD0: U1.53 (QSPI_SD0), U2.5 (DI(IO0))
/QSPI_SD1: U1.55 (QSPI_SD1), U2.2 (DO(IO1))
/QSPI_SD2: U1.54 (QSPI_SD2), U2.3 (IO2)
/QSPI_SD3: U1.51 (QSPI_SD3), U2.7 (IO3)
/QSPI_SS: R5.2, R6.1, U1.56 (QSPI_SS), U2.1 (~CS)
/RESET: J2.2, R4.1
/RUN: R4.2, U1.26 (RUN)
/SWCLK: J3.1, U1.24 (SWCLK)
/SWD: J3.3, U1.25 (SWD)
/USB_D+: J2.18, R1.2
/USB_D-: J2.19, R2.2
/USB_VBUS: DS1.2 (A), J2.20
/VSYS: C15.1, DS1.1 (K), J1.1, U3.1 (IN), U3.3 (EN)
/XIN: C12.2, U1.20 (XIN), Y1.1
/XOUT: R3.2, U1.21 (XOUT)
GND: C1.2, C2.2, C3.2, C4.2, C5.2, C6.2, C7.2, C8.2, C9.2, C10.2, C11.2, C12.1, C13.1, C14.2, C15.2, C16.2, C17.2, J1.3, J2.1, J2.17, J3.2, J3.MP (MountPin), U1.19 (TESTEN), U1.57 (GND), U2.4 (GND), U3.2 (GND), Y1.2, Y1.4
unnamed: C13.2, R3.1, Y1.3
unnamed: R1.1, U1.47 (USB_DP)
unnamed: R2.1, U1.46 (USB_DM)

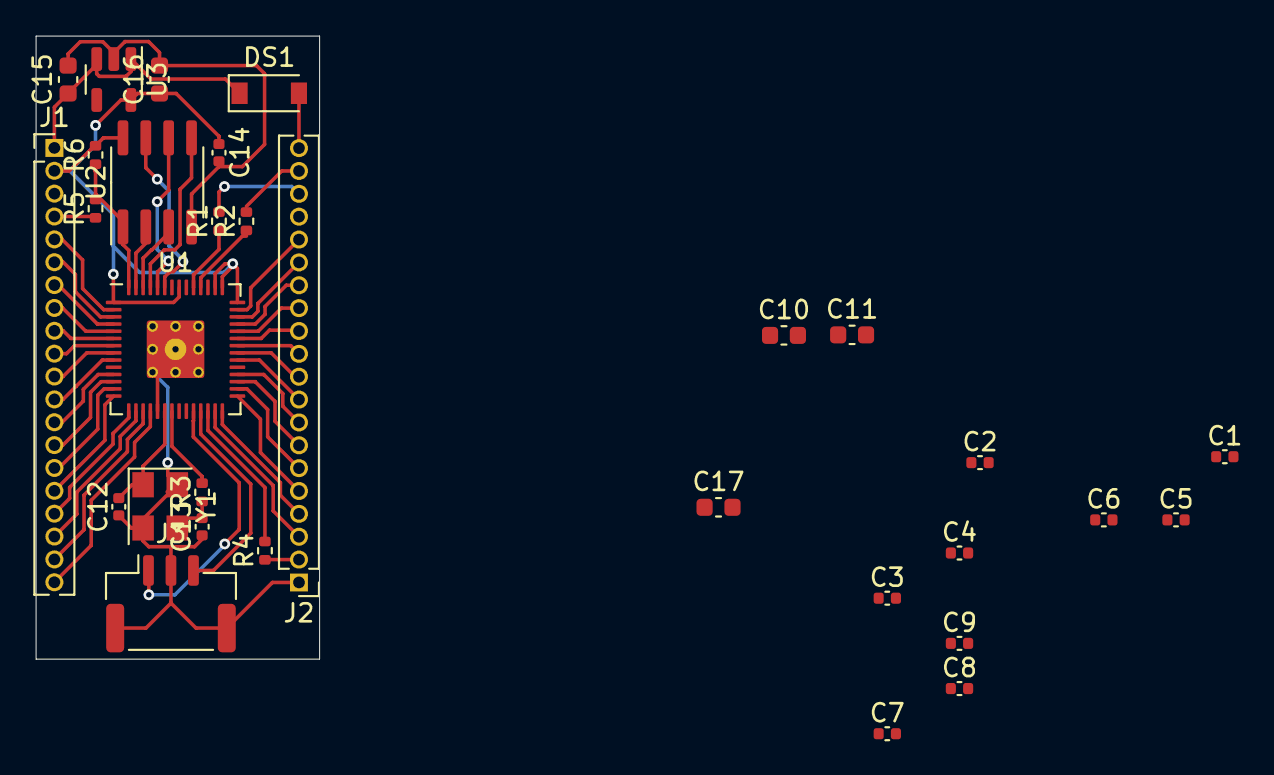
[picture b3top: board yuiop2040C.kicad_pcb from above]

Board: 2 copper layers, 15.7 x 34.6 mm, 31 parts (0 on the bottom side), 53 nets.
